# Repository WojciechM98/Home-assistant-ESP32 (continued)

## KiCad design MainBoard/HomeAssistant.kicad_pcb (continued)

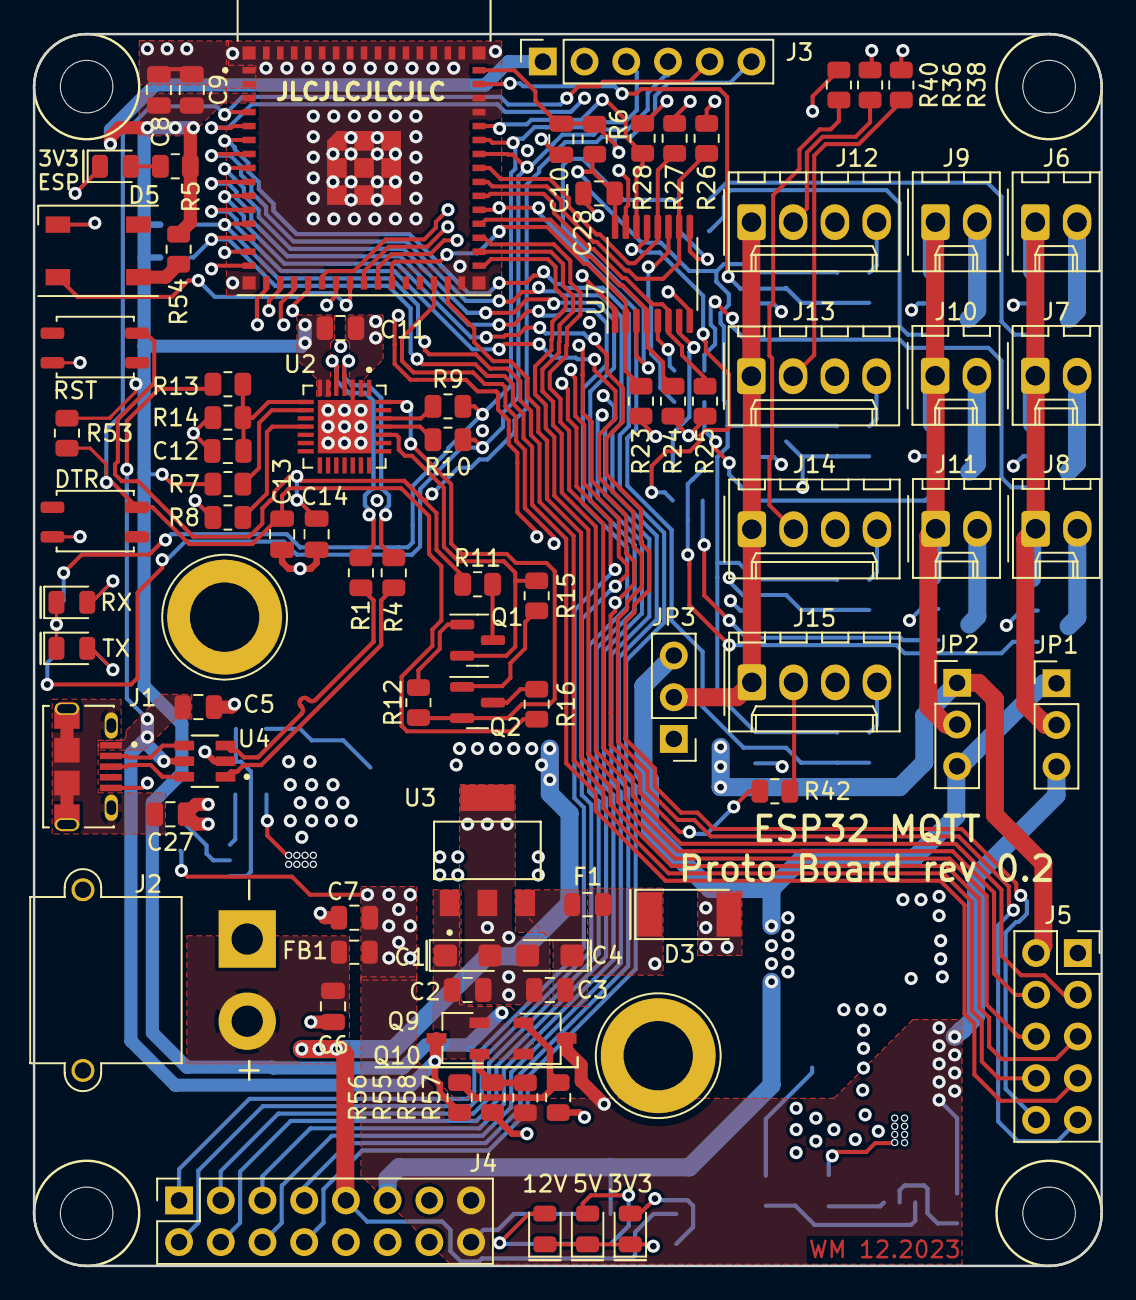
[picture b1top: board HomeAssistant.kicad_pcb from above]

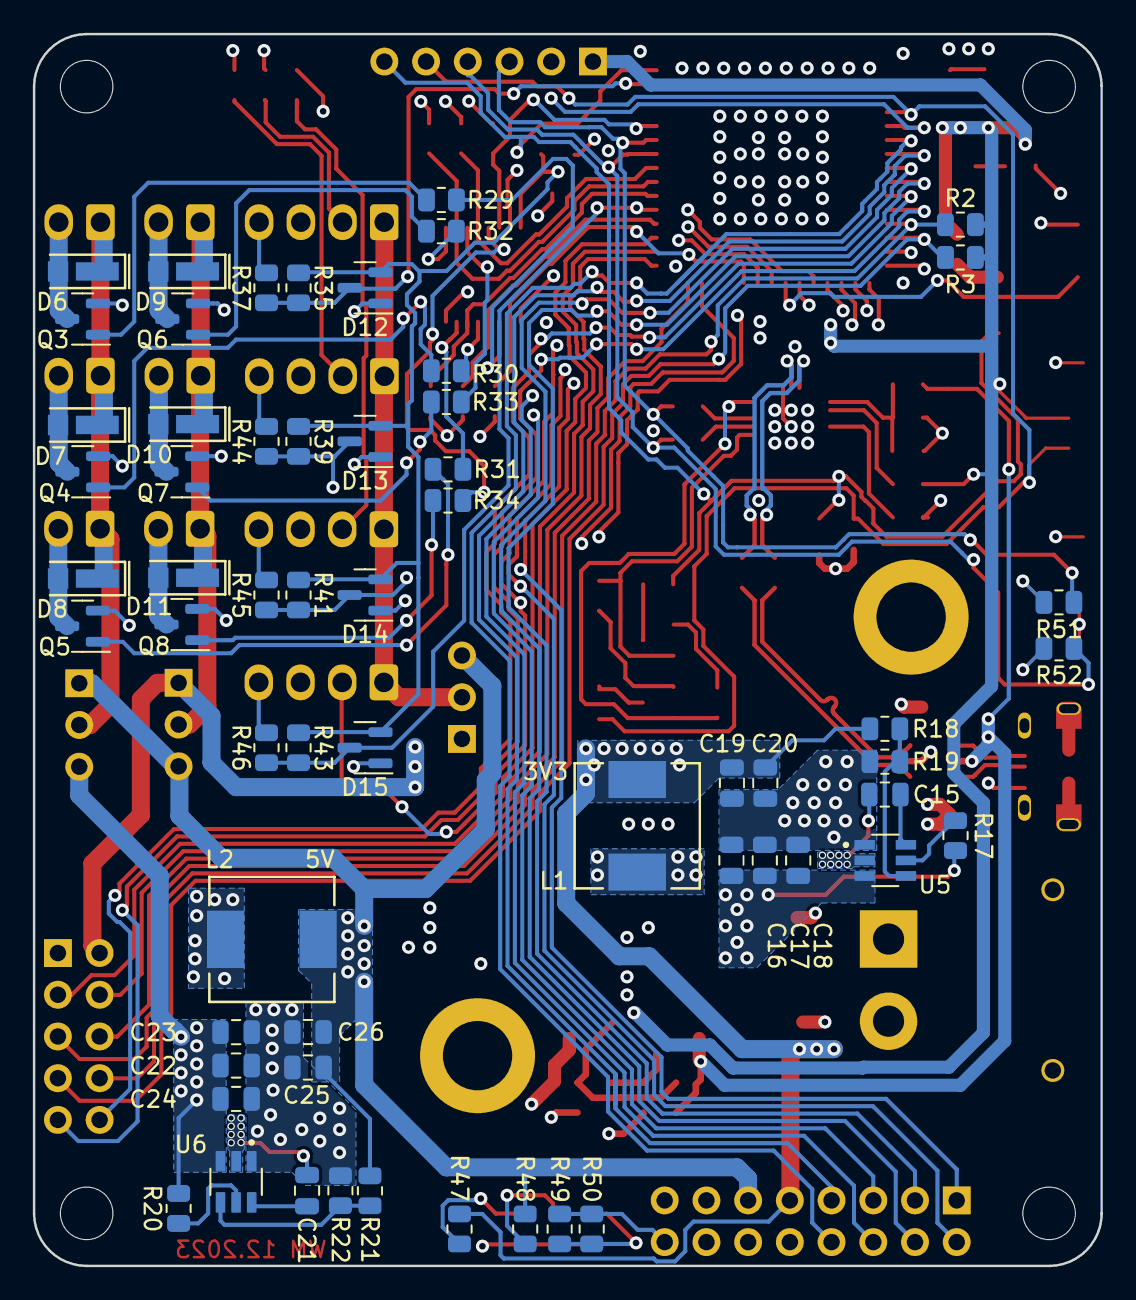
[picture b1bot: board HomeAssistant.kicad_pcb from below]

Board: 4 copper layers, 65.0 x 75.0 mm, 151 parts (60 on the bottom side), 91 nets.

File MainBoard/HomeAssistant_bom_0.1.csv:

Component,Description,Part,References,Value,Footprint,Quantity Per PCB,Datasheet,Availability,Check_prices,MANUFACTURER,MAXIMUM_PACKAGE_HEIGHT,MF,MP,PARTREV,Package,Price,Purchase-URL,STANDARD,SnapEDA_Link,AVAILABILITY,PACKAGE,PRICE,PURCHASE-URL
1,"Unpolarized capacitor, small symbol",C_Small,C2 C3 C9 C15 C18 C21 C24 C28,0.1uF/50V(10%),C_0805_2012Metric,8,~,,,,,,,,,,,,,,,,
2,"Unpolarized capacitor, small symbol",C_Small,C1 C4 C5 C8 C11 C16 C17 C19 C20 C22 C23 C25 C26,10uF/25V(20%),C_0805_2012Metric,13,~,,,,,,,,,,,,,,,,
3,"Unpolarized capacitor, small symbol",C_Small,C10 C12,1uF/16V(10%),C_0805_2012Metric,2,~,,,,,,,,,,,,,,,,
4,"Unpolarized capacitor, small symbol",C_Small,C27,4.7nF/25V(20%),C_0805_2012Metric,1,~,,,,,,,,,,,,,,,,
5,"Unpolarized capacitor, small symbol",C_Small,C13 C14,@0.1uF/50V(10%),C_0805_2012Metric,2,~,,,,,,,,,,,,,,,,
6,"Unpolarized capacitor, small symbol",C_Small,C6 C7,@2.2uF/50V(10%),C_0805_2012Metric,2,~,,,,,,,,,,,,,,,,
7,"Light emitting diode, small symbol",LED_Small,D4,3V3 RED,LED_0805_2012Metric,1,~,,,,,,,,,,,,,,,,
8,"Light emitting diode, small symbol",LED_Small,D16,3V3_ED RED,LED_0805_2012Metric,1,~,,,,,,,,,,,,,,,,
9,"Light emitting diode, small symbol",LED_Small,D17 D18,5V_ED RED,LED_0805_2012Metric,2,~,,,,,,,,,,,,,,,,
10,"Diode, small symbol",D_Small,D1,@CRS06,D_SOD-123F,1,~,,,,,,,,,,,,,,,,
11,40V 0.2A Dual Small Signal Schottky Diodes,BAS40-04,D12 D13 D14 D15,BAS40-04,SOT-23,4,http://www.vishay.com/docs/85701/bas40v.pdf,,,,,,,,,,,,,,,,
12,"Diode, small symbol",D_Small,D2,CRS06,D_SOD-123F,1,~,,,,,,,,,,,,,,,,
13,"Diode, small symbol",D_Small,D6 D7 D8 D9 D10 D11,DFLU1200-7,DIODE_DFLU1200_1P93X3_DIO,6,~,,,,,,,,,,,,,,,,
14,RGB LED with integrated controller,SK6812,D5,SK6812,LED_SK6812_PLCC4_5.0x5.0mm_P3.2mm,1,https://cdn-shop.adafruit.com/product-files/1138/SK6812+LED+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,,,,,,,,,,,,,,,,
15,"Zener diode, small symbol",D_Zener_Small,D3,ZM4729A-GS08,D_MELF,1,~,,,,,,,,,,,,,,,,
16,"Fuse, small symbol",Fuse_Small,F1,Fuse_Small,Fuse_0805_2012Metric,1,~,,,,,,,,,,,,,,,,
17,"Ferrite bead, small symbol",FerriteBead_Small,FB1,@BLM21SN300SN1D,Fuse_0805_2012Metric,1,~,,,,,,,,,,,,,,,,
18,,10118194-0001LF,J1,10118194-0001LF,USB_AMPHENOL_10118194-0001LF,1,,In Stock,https://www.snapeda.com/parts/10118194-0001LF/Amphenol+FCI/v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,Amphenol ICC,2.66 mm,Amphenol ICC,10118194-0001LF,D,None,None,https://www.snapeda.com/api/url_track_click_mouser/?unipart_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 ICC&part_name=10118194-0001LF&search_term=None,Manufacturer Recommendations,https://www.snapeda.com/parts/10118194-0001LF/Amphenol+FCI/v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,,,,
19,"Generic connector, single row, 01x02, script generated (kicad-library-utils/schlib/autogen/connector/)",Conn_01x02,J6 J7 J8 J9 J10 J11,Conn_01x02,Molex_KK-254_AE-6410-02A_1x02_P2.54mm_Vertical,6,~,,,,,,,,,,,,,,,,
20,"Generic connector, single row, 01x04, script generated (kicad-library-utils/schlib/autogen/connector/)",Conn_01x04,J12 J13 J14 J15,Conn_01x04,Molex_KK-254_AE-6410-04A_1x04_P2.54mm_Vertical,4,~,,,,,,,,,,,,,,,,
21,"Generic connector, single row, 01x06, script generated (kicad-library-utils/schlib/autogen/connector/)",Conn_01x06,J3,Conn_01x06,PinSocket_1x06_P2.54mm_Vertical,1,~,,,,,,,,,,,,,,,,
22,"Generic connector, double row, 02x05, odd/even pin numbering scheme (row 1 odd numbers, row 2 even numbers), script generated (kicad-library-utils/schlib/autogen/connector/)",Conn_02x05_Odd_Even,J5,Conn_02x05_Odd_Even,PinSocket_2x05_P2.54mm_Vertical,1,~,,,,,,,,,,,,,,,,
23,"Generic connector, double row, 02x08, odd/even pin numbering scheme (row 1 odd numbers, row 2 even numbers), script generated (kicad-library-utils/schlib/autogen/connector/)",Conn_02x08_Odd_Even,J4,Conn_02x08_Odd_Even,PinSocket_2x08_P2.54mm_Vertical,1,~,,,,,,,,,,,,,,,,
24,"Generic connector, single row, 01x02, script generated (kicad-library-utils/schlib/autogen/connector/)",Conn_01x02,J2,XT30PW-M,AMASS_XT30PW-M_1x02_P2.50mm_Horizontal,1,~,,,,,,,,,,,,,,,,
25,"Jumper, 3-pole, both open",Jumper_3_Open,JP1 JP2 JP3,Jumper_3_Open,PinHeader_1x03_P2.54mm_Vertical,3,~,,,,,,,,,,,,,,,,
26,"Inductor, small symbol",L_Small,L1 L2,3.3uH,INDM7676X355N,2,~,,,,,,,,,,,,,,,,
27,"0.1A Ic, 30V Vce, NPN Transistor, SOT-23",BC848,Q1 Q2,BC848,SOT-23,2,http://www.infineon.com/dgdl/Infineon-BC847SERIES_BC848SERIE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,,,,,,,,,,,,,,,,
28,"0.115A Id, 60V Vds, N-Channel MOSFET, SOT-23",2N7002,Q3 Q4 Q5 Q6 Q7 Q8,DMN3023L,SOT-23,6,https://www.onsemi.com/pub/Collateral/NDS7002A-D.PDF,,,,,,,,,,,,,,,,
29,"Resistor, small symbol",R_Small,R37 R44 R45 R46,10R,R_0805_2012Metric,4,~,,,,,,,,,,,,,,,,
30,"Resistor, small symbol",R_Small,R5 R47,62R,R_0805_2012Metric,2,~,,,,,,,,,,,,,,,,
31,"Resistor, small symbol",R_Small,R48,150R,R_0805_2012Metric,1,~,,,,,,,,,,,,,,,,
32,"Resistor, small symbol",R_Small,R36 R38 R40 R42,470R,R_0805_2012Metric,4,~,,,,,,,,,,,,,,,,
33,"Resistor, small symbol",R_Small,R35 R39 R41 R43,100K,R_0805_2012Metric,4,~,,,,,,,,,,,,,,,,
34,"Resistor, small symbol",R_Small,R1 R4 R9 R10 R11 R16,0R(1%),R_0805_2012Metric,6,~,,,,,,,,,,,,,,,,
35,"Resistor, small symbol",R_Small,R6 R12 R15 R17 R19 R20 R22 R23 R24 R25 R26 R27 R28,10K(1%),R_0805_2012Metric,13,~,,,,,,,,,,,,,,,,
36,"Resistor, small symbol",R_Small,R2 R3 R7 R29 R30 R31 R32 R33 R34 R49 R50,1K(1%),R_0805_2012Metric,11,~,,,,,,,,,,,,,,,,
37,"Resistor, small symbol",R_Small,R13,22.1K(1%),R_0805_2012Metric,1,~,,,,,,,,,,,,,,,,
38,"Resistor, small symbol",R_Small,R18,33.2K(1%),R_0805_2012Metric,1,~,,,,,,,,,,,,,,,,
39,"Resistor, small symbol",R_Small,R14,47.5K(1%),R_0805_2012Metric,1,~,,,,,,,,,,,,,,,,
40,"Resistor, small symbol",R_Small,R21,54.9K(1%),R_0805_2012Metric,1,~,,,,,,,,,,,,,,,,
41,"Resistor, small symbol",R_Small,R8,@10K(1%),R_0805_2012Metric,1,~,,,,,,,,,,,,,,,,
42,,EVQP2202M_1,SW1,EVQP2202M,TACT_EVQP2202M,1,,,,,,,,,,,,,,,,,
43,,EVQP2202M,SW2,EVQP2202M,TACT_EVQP2202M,1,,,,,,,,,,,,,,,,,
44,,CP2102N-A02-GQFN28,U2,CP2102N-A02-GQFN28,QFN50P500X500X80-29N,1,,In Stock,https://www.snapeda.com/parts/CP2102N-A02-GQFN28/Silicon+Lab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,Silicon Labs,0.8 mm,Silicon Labs,CP2102N-A02-GQFN28,1.5,WFQFN-28 Silicon Labs,None,https://www.snapeda.com/api/url_track_click_mouser/?unipart_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 Labs&part_name=CP2102N-A02-GQFN28&search_term=None,IPC 7351B,https://www.snapeda.com/parts/CP2102N-A02-GQFN28/Silicon+Lab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,,,,
45,,ESP32-S2-MINI-1,U1,ESP32-S2-MINI-1,XCVR_ESP32-S2-MINI-1,1,,Not in stock,https://www.snapeda.com/parts/ESP32-S2-MINI-1/Espressif+Syst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,Espressif Systems,2.55mm,Espressif Systems,ESP32-S2-MINI-1,1.0,NON STANDARD-65 Espressif Systems,None,,Manufacturer Recommendations,https://www.snapeda.com/parts/ESP32-S2-MINI-1/Espressif+Syst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,,,,
46,,LD1117AS33TR,U3,LD1117AS33TR,SOT-223_STM,1,LD1117AS33TR,,,,,,,,,,,,,,,,
47,,MC74HC365A,U7,MC74HC365A,TSSOP-16_4.4x5mm_P0.65mm,1,,,,,,,,,,,,,,,,,
48,,TPS563201DDCR,U5 U6,TPS563201DDCR,SOT95P280X110-6N,2,,In Stock,https://www.snapeda.com/parts/TPS563201DDCR/Texas+Instrument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,Texas Instruments,1.10mm,Texas Instruments,TPS563201DDCR,December 2015,SOT-23-THN-6 Texas Instruments,None,https://www.snapeda.com/api/url_track_click_mouser/?unipart_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 Instruments&part_name=TPS563201DDCR&search_term=None,IPC-7351B,https://www.snapeda.com/parts/TPS563201DDCR/Texas+Instrument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,,,,
49,,USBLC6-2SC6,U4,USBLC6-2SC6Y,SOT95P280X145-6N,1,,In Stock,https://www.snapeda.com/parts/USBLC6-2SC6/STMicroelectronics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,,,STMicroelectronics,USBLC6-2SC6,,SOT-23-6 STMicroelectronics,None,https://pricing.snapeda.com/search/part/USBLC6-2SC6/?ref=eda,,https://www.snapeda.com/parts/USBLC6-2SC6/STMicroelectronics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,In Stock,SOT-23-6 STMicroelectronics,None,https://pricing.snapeda.com/search/part/USBLC6-2SC6/?ref=eda





Component Groups:,49
Component Count:,135
Fitted Components:,135
Number of PCBs:,1
Total components:,135
Schematic Version:,0.1
Schematic Date:,2023-12-28
PCB Variant:,default
BoM Date:,04.01.2024 09:28:53
Schematic Source:,HomeAssistant.kicad_sch
KiCad Version:,Eeschema (6.0.6)

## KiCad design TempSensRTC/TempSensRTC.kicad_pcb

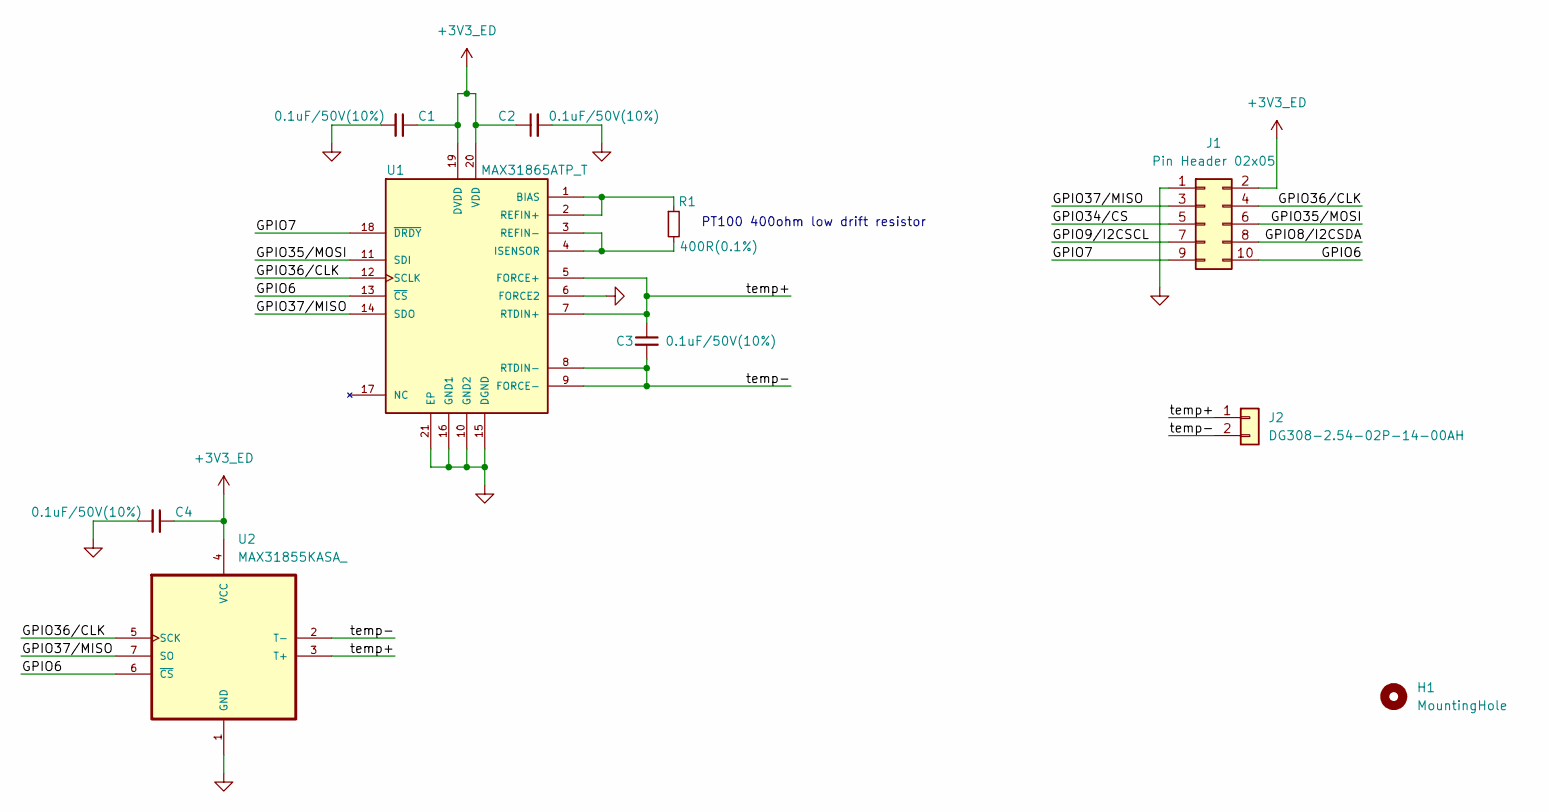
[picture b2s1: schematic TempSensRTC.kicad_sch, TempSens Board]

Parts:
C1, C2, C3, C4: 0.1uF/50V(10%); C_0805_2012Metric
H1: MountingHole; MountingHole_2.7mm_M2.5
J1: Pin Header 02x05; PinHeader_2x05_P2.54mm_Vertical
J2: DG308-2.54-02P-14-00AH; Molex_KK-254_AE-6410-02A_1x02_P2.54mm_Vertical
R1: 400R(0.1%); R_0805_2012Metric
U1: MAX31865ATP_T; QFN65P500X500X80-21N; PARTREV 3
U2: MAX31855KASA_; SOIC127P600X175-8N

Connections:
+3V3_ED: C1.1, C2.1, C4.1, J1.2, U1.19 (DVDD), U1.20 (VDD), U2.4 (VCC)
/GPIO6: J1.10, U1.13 (~CS), U2.6 (~CS)
/GPIO7: J1.9, U1.18 (~DRDY)
/GPIO8/I2CSDA: J1.8
/GPIO9/I2CSCL: J1.7
/GPIO34/CS: J1.5
/GPIO35/MOSI: J1.6, U1.11 (SDI)
/GPIO36/CLK: J1.4, U1.12 (SCLK), U2.5 (SCK)
/GPIO37/MISO: J1.3, U1.14 (SDO), U2.7 (SO)
/temp+: C3.1, J2.1, U1.5 (FORCE+), U1.7 (RTDIN+), U2.3 (T+)
/temp-: C3.2, J2.2, U1.8 (RTDIN-), U1.9 (FORCE-), U2.2 (T-)
GND: C1.2, C2.2, C4.2, J1.1, U1.6 (FORCE2), U1.10 (GND2), U1.15 (DGND), U1.16 (GND1), U1.21 (EP), U2.1 (GND)
unnamed: R1.1, U1.1 (BIAS), U1.2 (REFIN+)
unnamed: R1.2, U1.3 (REFIN-), U1.4 (ISENSOR)

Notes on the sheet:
PT100 400ohm low drift resistor

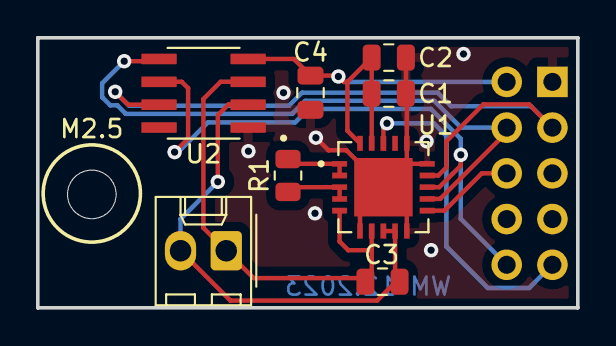
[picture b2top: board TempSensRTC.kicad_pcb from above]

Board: 2 copper layers, 30.0 x 15.0 mm, 10 parts (1 on the bottom side), 11 nets.

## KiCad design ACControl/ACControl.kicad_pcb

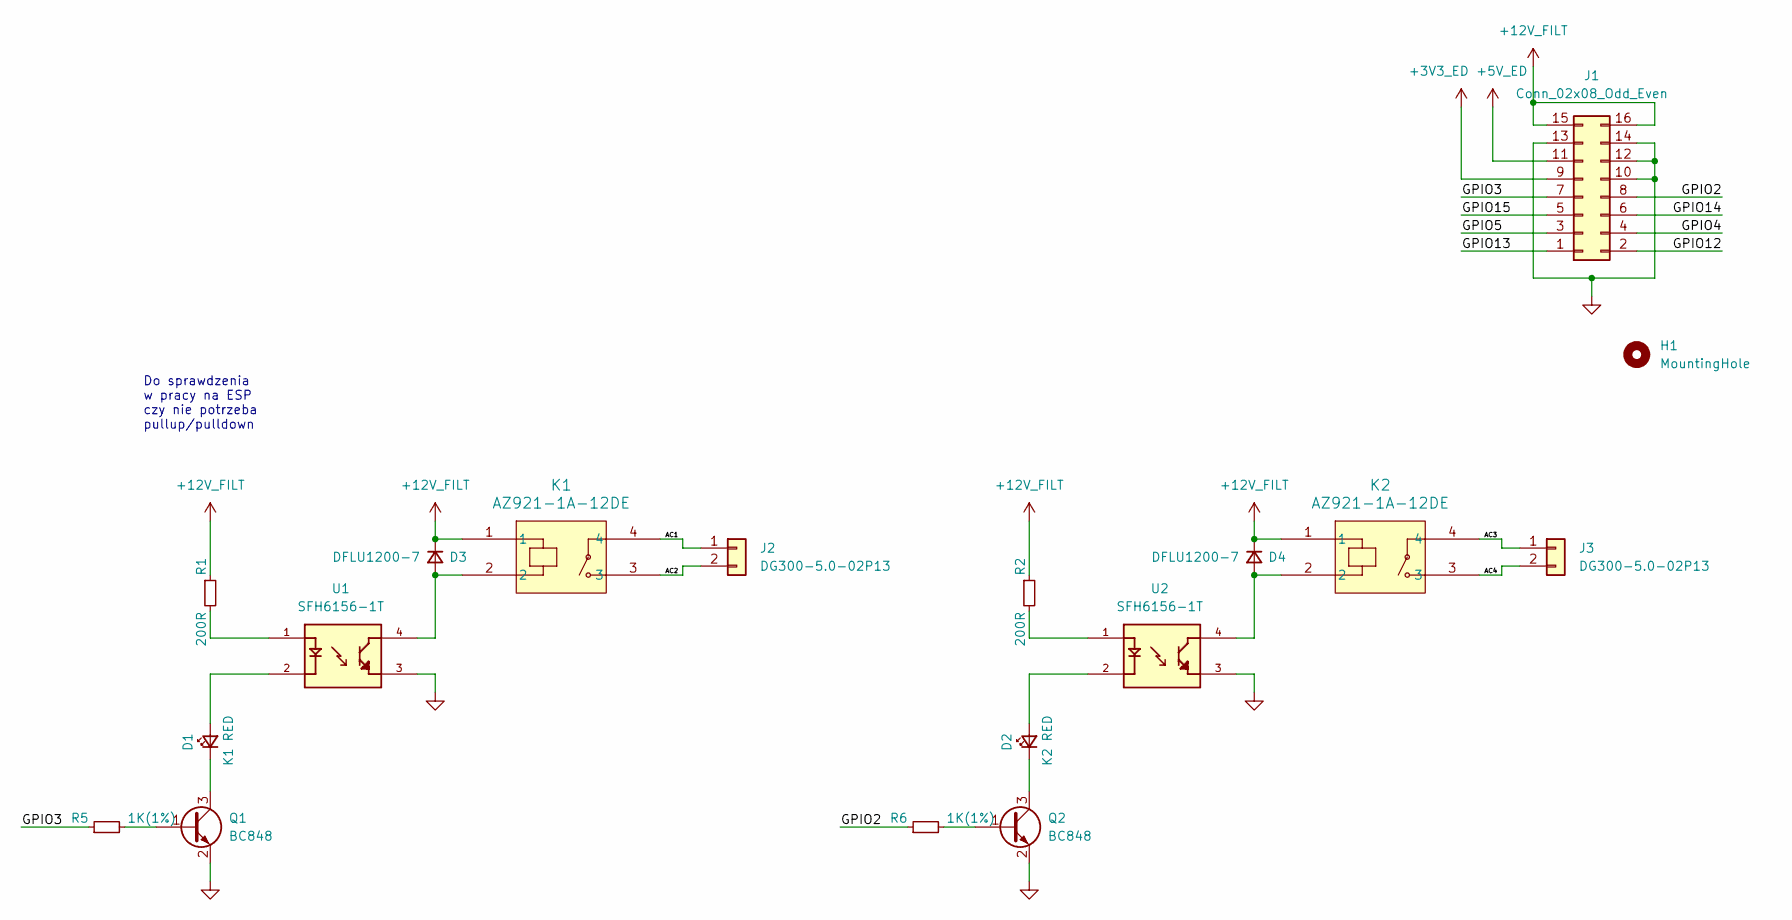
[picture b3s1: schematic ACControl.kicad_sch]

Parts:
D1: K1 RED; LED_0805_2012Metric
D2: K2 RED; LED_0805_2012Metric
D3, D4: DFLU1200-7; DIODE_DFLU1200_1P93X3_DIO
H1: MountingHole; MountingHole_2.7mm_M2.5
J1: Conn_02x08_Odd_Even; PinHeader_2x08_P2.54mm_Vertical
J2, J3: DG300-5.0-02P13; DG300-5.0-2P
K1, K2: AZ921-1A-12DE; SIP4_AZ921_AMZ
Q1, Q2: BC848; SOT-23
R1, R2: 200R; R_0805_2012Metric
R5, R6: 1K(1%); R_0805_2012Metric
U1, U2: SFH6156-1T; DIGI-KEY_PART_NUMBER 751-1346-1-ND

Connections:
+3V3_ED: J1.9
+5V_ED: J1.11
+12V_FILT: D3.1 (K), D4.1 (K), J1.15, J1.16, K1.1, K2.1, R1.1, R2.1
/AC1: J2.1, K1.4
/AC2: J2.2, K1.3
/AC3: J3.1, K2.4
/AC4: J3.2, K2.3
/GPIO2: J1.8, R6.1
/GPIO3: J1.7, R5.1
/GPIO4: J1.4
/GPIO5: J1.3
/GPIO12: J1.2
/GPIO13: J1.1
/GPIO14: J1.6
/GPIO15: J1.5
GND: J1.10, J1.12, J1.13, J1.14, Q1.2 (E), Q2.2 (E), U1.3, U2.3
unnamed: D1.1 (K), Q1.3 (C)
unnamed: D2.1 (K), Q2.3 (C)
unnamed: Q1.1 (B), R5.2
unnamed: Q2.1 (B), R6.2
unnamed: R1.2, U1.1
unnamed: D1.2 (A), U1.2
unnamed: D3.2 (A), K1.2, U1.4
unnamed: R2.2, U2.1
unnamed: D2.2 (A), U2.2
unnamed: D4.2 (A), K2.2, U2.4

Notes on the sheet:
Do sprawdzenia w pracy na ESP czy nie potrzeba pullup/pulldown

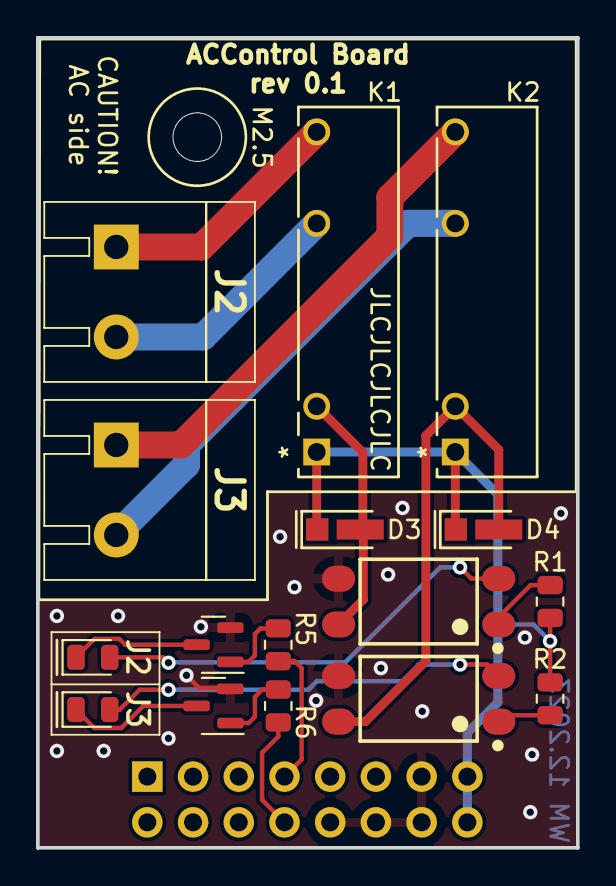
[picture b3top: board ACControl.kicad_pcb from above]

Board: 2 copper layers, 30.0 x 45.0 mm, 18 parts (1 on the bottom side), 18 nets.

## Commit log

2024-01-30 Added files
2024-02-04 Structure changes to schematic files
2024-02-04 Adding real example photos
2024-02-04 Photos added
2024-07-14 revision 0.2
2024-07-14 Resolved problem with .jpg files
